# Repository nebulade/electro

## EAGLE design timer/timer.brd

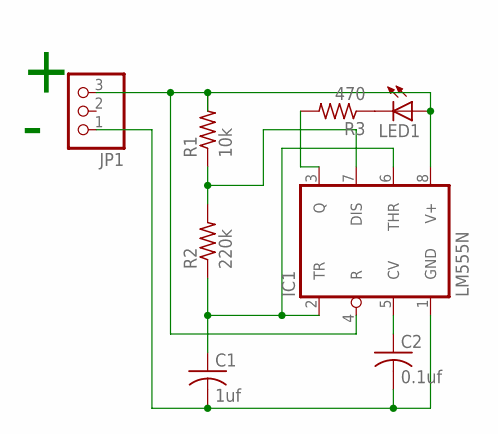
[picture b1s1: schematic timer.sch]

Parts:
C1: 1uf; C050-025X075
C2: 0.1uf; C050-025X075
IC1: LM555N; DIL08-ROUND
JP1: PINHD-1X3; 1X03
LED1: LED5MM
R1: 10k; 0309/10
R2: 220k; 0309/10
R3: 470; 0309/10

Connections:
unnamed: C2.1, IC1.5 (CV)
unnamed: LED1.K (C), R3.1
unnamed: IC1.7 (DIS), R1.1, R2.2
unnamed: IC1.3 (Q), R3.2
unnamed: C1.2, C2.2, IC1.1 (GND), JP1.1
unnamed: IC1.4 (R), IC1.8 (V+), JP1.3, LED1.A, R1.2
unnamed: C1.1, IC1.2 (TR), IC1.6 (THR), R2.1

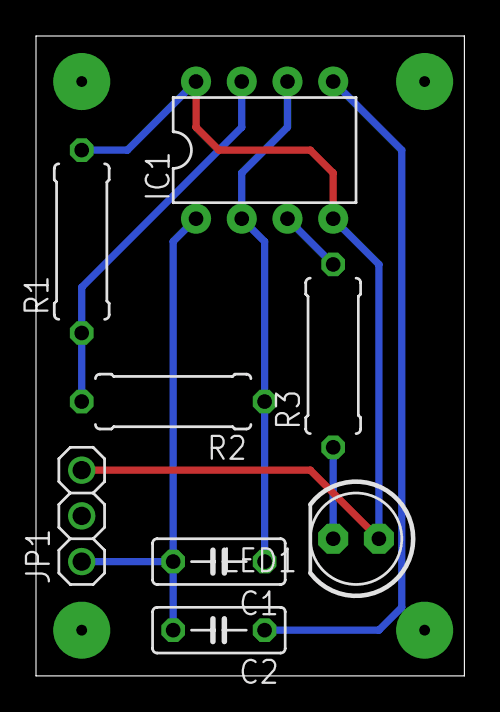
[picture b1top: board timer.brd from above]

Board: 2 copper layers, 23.8 x 35.5 mm, 8 parts (0 on the bottom side), 7 nets.

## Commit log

2012-10-29 add mounting holes
2012-10-29 improve packing
2012-10-29 update dmx shield
2012-10-29 use on board IC
2012-10-29 adjust parts description
2012-10-29 change all components to surface mounted
2012-10-29 downgrade to version 5
2012-10-29 generate initial board layout
2012-11-04 board routed
2012-11-06 minor updates to the board design
2012-11-19 adjust board layout
2012-11-19 some more prettifying
